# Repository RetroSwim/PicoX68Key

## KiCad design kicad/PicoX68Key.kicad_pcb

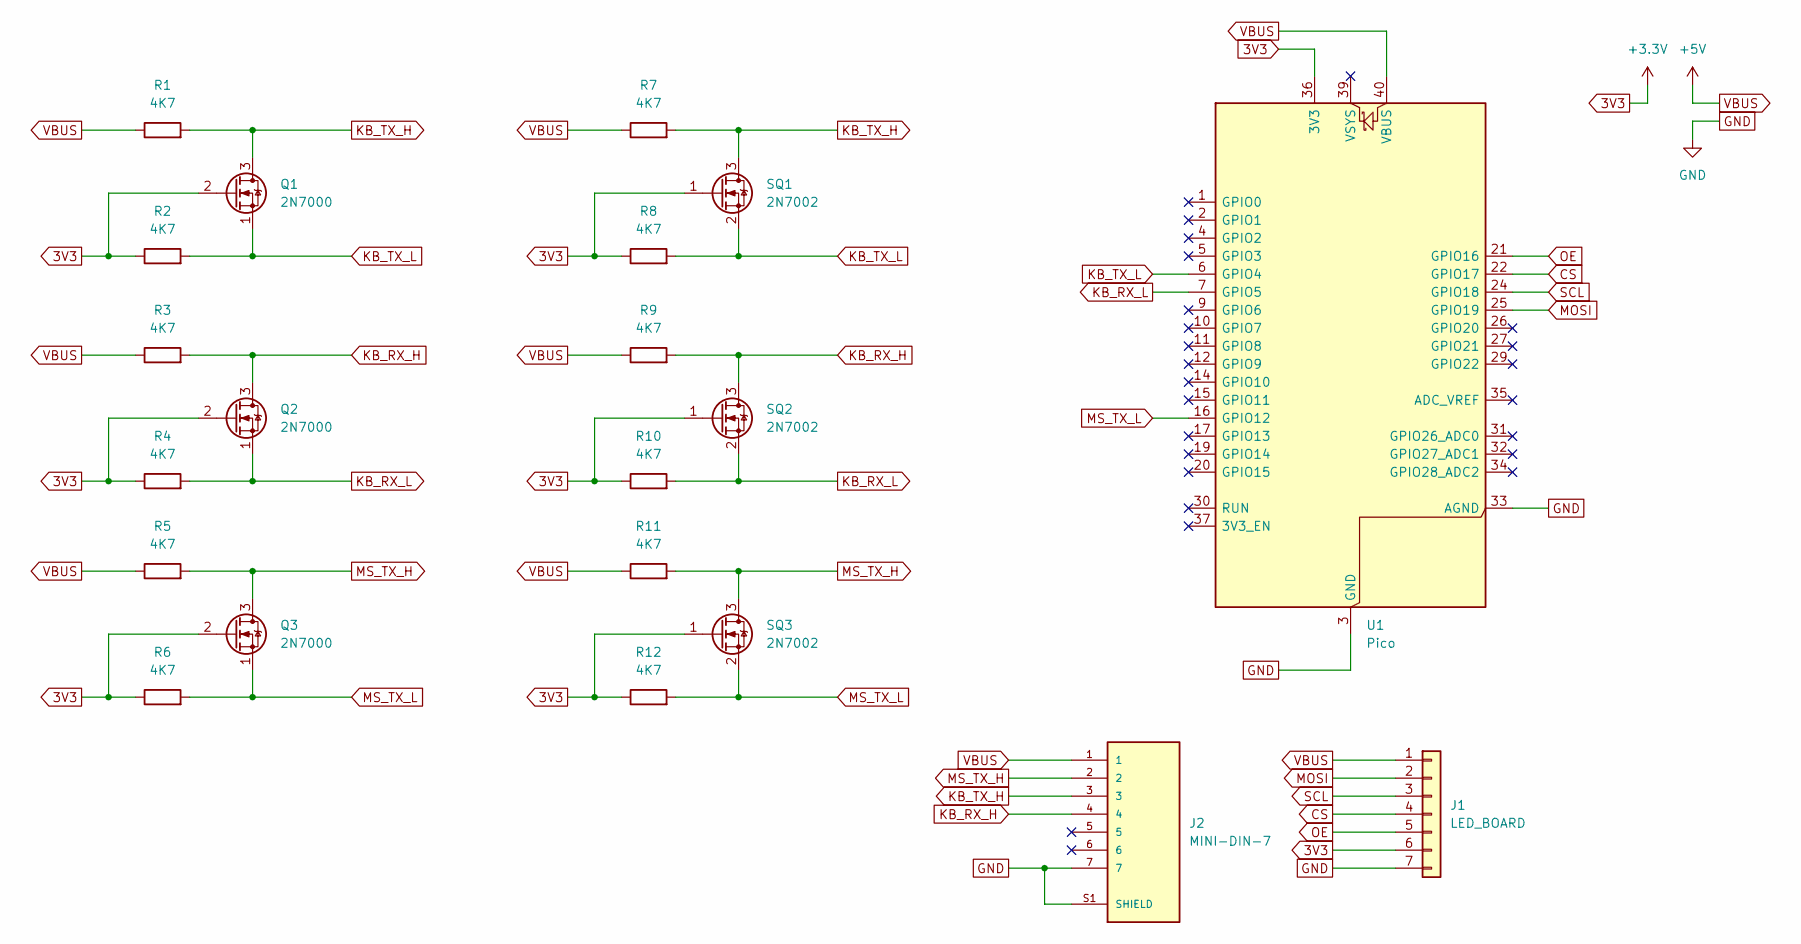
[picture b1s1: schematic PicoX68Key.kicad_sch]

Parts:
J1: LED_BOARD; PinSocket_1x07_P2.54mm_Vertical
J2: MINI-DIN-7; Mini_DIN_round_7_canned; PARTREV 02/18/2022
Q1, Q2, Q3: 2N7000; TO-92L_Inline_Wide
R1, R2, R3, R4, R5, R6: 4K7; R_Axial_DIN0309_L9.0mm_D3.2mm_P12.70mm_Horizontal
R7, R8, R9, R10, R11, R12: 4K7; R_1206_3216Metric_Pad1.30x1.75mm_HandSolder
SQ1, SQ2, SQ3: 2N7002; SOT-23
U1: Pico; RaspberryPi_Pico_Common

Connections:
3V3: J1.6, Q1.2 (G), Q2.2 (G), Q3.2 (G), R2.1, R4.1, R6.1, R8.1, R10.1, R12.1, SQ1.1 (G), SQ2.1 (G), SQ3.1 (G), U1.36 (3V3)
CS: J1.4, U1.22 (GPIO17)
GND: J1.7, J2.7, J2.S1 (SHIELD), U1.3 (GND), U1.8 (GND), U1.13 (GND), U1.18 (GND), U1.23 (GND), U1.28 (GND), U1.33 (AGND), U1.38 (GND)
KB_RX_H: J2.4, Q2.3 (D), R3.2, R9.2, SQ2.3 (D)
KB_RX_L: Q2.1 (S), R4.2, R10.2, SQ2.2 (S), U1.7 (GPIO5)
KB_TX_H: J2.3, Q1.3 (D), R1.2, R7.2, SQ1.3 (D)
KB_TX_L: Q1.1 (S), R2.2, R8.2, SQ1.2 (S), U1.6 (GPIO4)
MOSI: J1.2, U1.25 (GPIO19)
MS_TX_H: J2.2, Q3.3 (D), R5.2, R11.2, SQ3.3 (D)
MS_TX_L: Q3.1 (S), R6.2, R12.2, SQ3.2 (S), U1.16 (GPIO12)
OE: J1.5, U1.21 (GPIO16)
SCL: J1.3, U1.24 (GPIO18)
VBUS: J1.1, J2.1, R1.1, R3.1, R5.1, R7.1, R9.1, R11.1, U1.40 (VBUS)

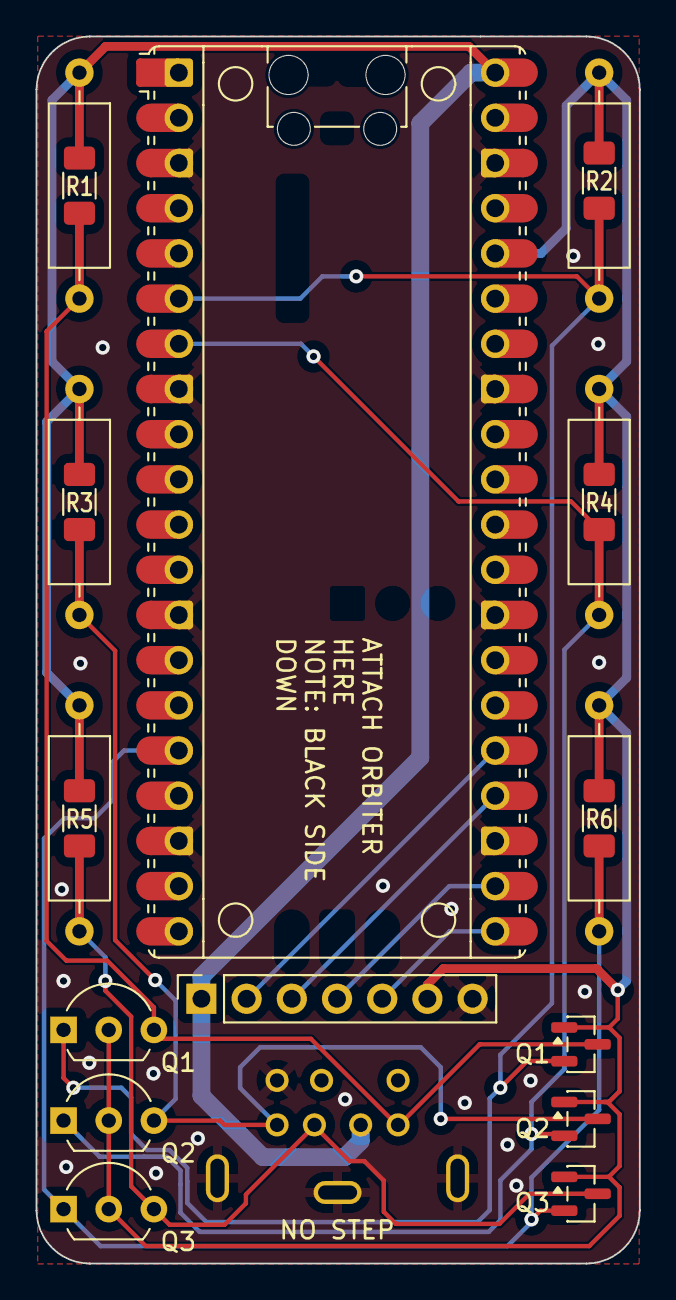
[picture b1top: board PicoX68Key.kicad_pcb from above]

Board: 2 copper layers, 33.9 x 69.0 mm, 21 parts (0 on the bottom side), 13 nets.

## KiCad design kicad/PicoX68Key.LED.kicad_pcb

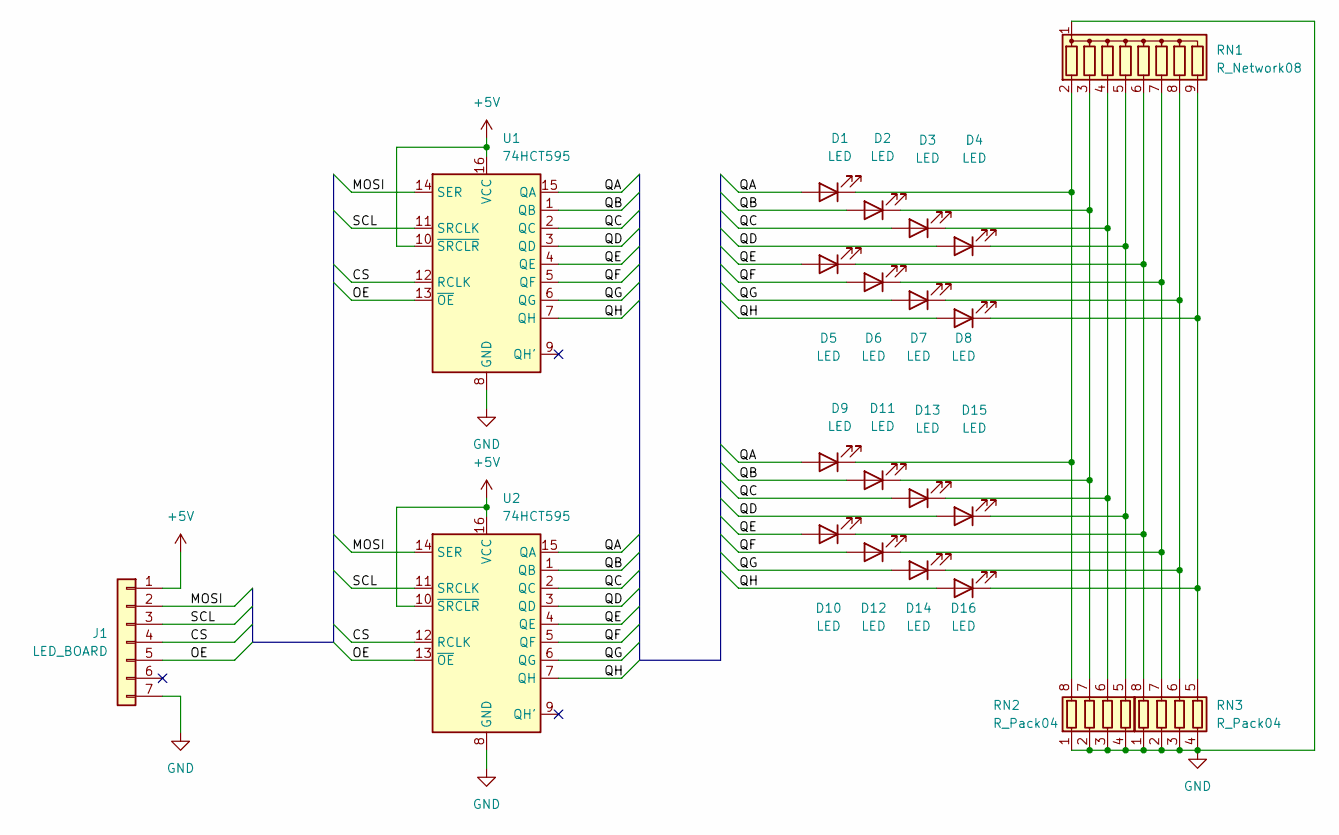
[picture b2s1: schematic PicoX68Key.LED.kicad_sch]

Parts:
D1, D2, D3, D4, D5, D6, D7, D8: LED; LED_D5.0mm
D9, D10, D11, D12, D13, D14, D15, D16: LED; LED_1206_3216Metric
J1: LED_BOARD; PinSocket_1x07_P2.54mm_Vertical
RN1: R_Network08; R_Array_SIP9
RN2, RN3: R_Pack04
U1: 74HCT595; DIP-16_W7.62mm
U2: 74HCT595; SO-16_3.9x9.9mm_P1.27mm

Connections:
+5V: J1.1, U1.10 (~SRCLR), U1.16 (VCC), U2.10 (~SRCLR), U2.16 (VCC)
/CS: J1.4, U1.12 (RCLK), U2.12 (RCLK)
/MOSI: J1.2, U1.14 (SER), U2.14 (SER)
/OE: J1.5, U1.13 (~OE), U2.13 (~OE)
/QA: D1.2 (A), D9.2 (A), U1.15 (QA), U2.15 (QA)
/QB: D2.2 (A), D11.2 (A), U1.1 (QB), U2.1 (QB)
/QC: D3.2 (A), D13.2 (A), U1.2 (QC), U2.2 (QC)
/QD: D4.2 (A), D15.2 (A), U1.3 (QD), U2.3 (QD)
/QE: D5.2 (A), D10.2 (A), U1.4 (QE), U2.4 (QE)
/QF: D6.2 (A), D12.2 (A), U1.5 (QF), U2.5 (QF)
/QG: D7.2 (A), D14.2 (A), U1.6 (QG), U2.6 (QG)
/QH: D8.2 (A), D16.2 (A), U1.7 (QH), U2.7 (QH)
/SCL: J1.3, U1.11 (SRCLK), U2.11 (SRCLK)
GND: J1.7, RN1.1 (common), RN2.1 (R1.1), RN2.2 (R2.1), RN2.3 (R3.1), RN2.4 (R4.1), RN3.1 (R1.1), RN3.2 (R2.1), RN3.3 (R3.1), RN3.4 (R4.1), U1.8 (GND), U2.8 (GND)
unnamed: D1.1 (K), D9.1 (K), RN1.2 (R1), RN2.8 (R1.2)
unnamed: D5.1 (K), D10.1 (K), RN1.6 (R5), RN3.8 (R1.2)
unnamed: D2.1 (K), D11.1 (K), RN1.3 (R2), RN2.7 (R2.2)
unnamed: D6.1 (K), D12.1 (K), RN1.7 (R6), RN3.7 (R2.2)
unnamed: D3.1 (K), D13.1 (K), RN1.4 (R3), RN2.6 (R3.2)
unnamed: D7.1 (K), D14.1 (K), RN1.8 (R7), RN3.6 (R3.2)
unnamed: D4.1 (K), D15.1 (K), RN1.5 (R4), RN2.5 (R4.2)
unnamed: D8.1 (K), D16.1 (K), RN1.9 (R8), RN3.5 (R4.2)

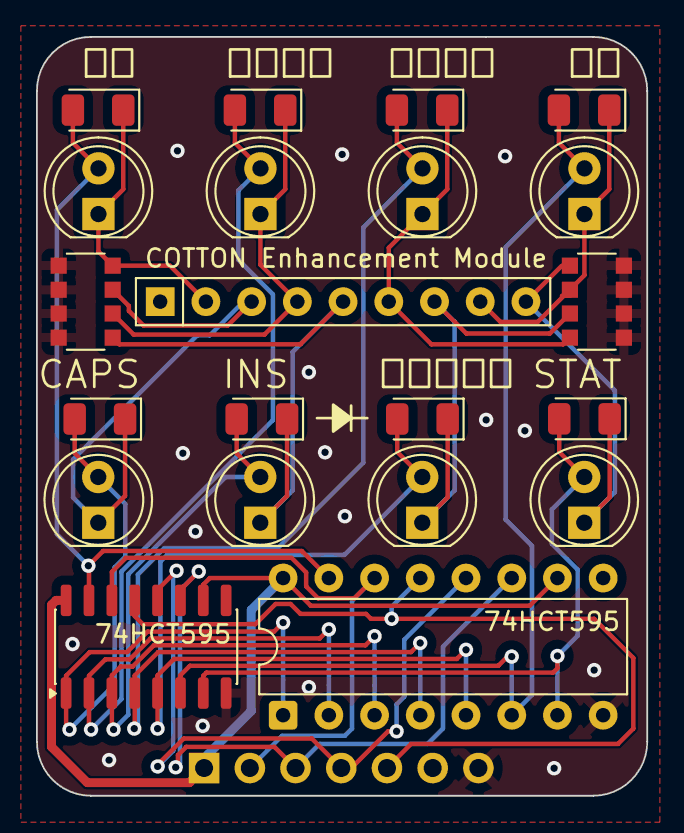
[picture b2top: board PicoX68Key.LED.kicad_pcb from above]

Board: 2 copper layers, 33.9 x 42.2 mm, 22 parts (1 on the bottom side), 22 nets.

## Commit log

2025-11-25 Cherry-pick code changes from kicad branch
2025-11-25 Cherrypick gitignore
2025-11-26 Minor layout tweaks
2025-12-02 Add LED sub-board
2025-12-24 Create LED board and tweak designs
2025-12-24 Changed some settings to make 3D view look better
2026-01-03 Fixed LED sub board code
2026-01-03 Fix some project problems
2026-01-03 gitignore updates
2026-01-03 Update gitignore
2026-01-03 Fix typo in status led control
2026-01-03 Fixed B2B interconnect clearance
2026-01-04 Fix ground plane
2026-01-04 Add PWM functionality to set LED brightness
2026-01-04 Add label for OE/PWM pin on interconnect
2026-01-04 Updated credits
2026-01-07 Changes to enable brightness control. Final PCB polish.
